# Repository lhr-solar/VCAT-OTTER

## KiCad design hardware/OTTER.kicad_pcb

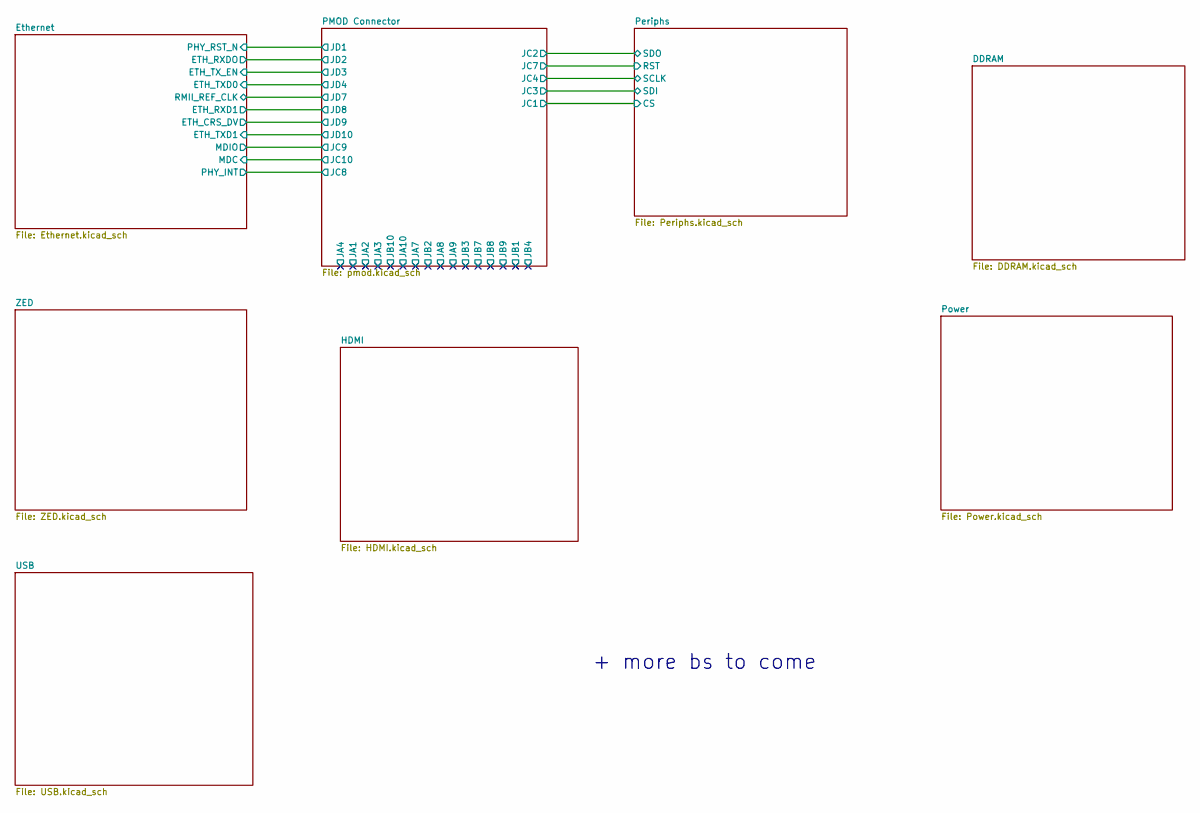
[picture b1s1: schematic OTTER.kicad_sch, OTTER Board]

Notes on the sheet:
+ more bs to come

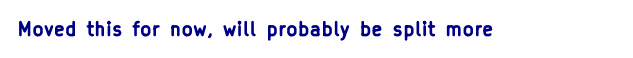
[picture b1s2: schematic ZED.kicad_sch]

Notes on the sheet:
Moved this for now, will probably be split more

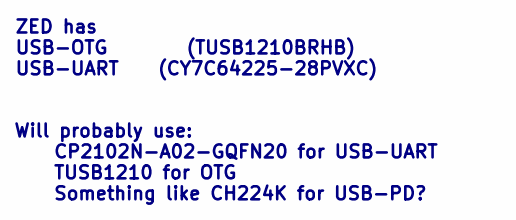
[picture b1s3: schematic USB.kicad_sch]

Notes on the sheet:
ZED has USB-OTG (TUSB1210BRHB) USB-UART (CY7C64225-28PVXC)
Will probably use: CP2102N-A02-GQFN20 for USB-UART TUSB1210 for OTG Something like CH224K for USB-PD?

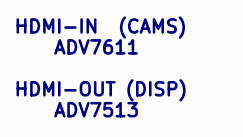
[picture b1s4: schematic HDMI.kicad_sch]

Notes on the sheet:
HDMI-IN (CAMS) ADV7611 HDMI-OUT (DISP) ADV7513

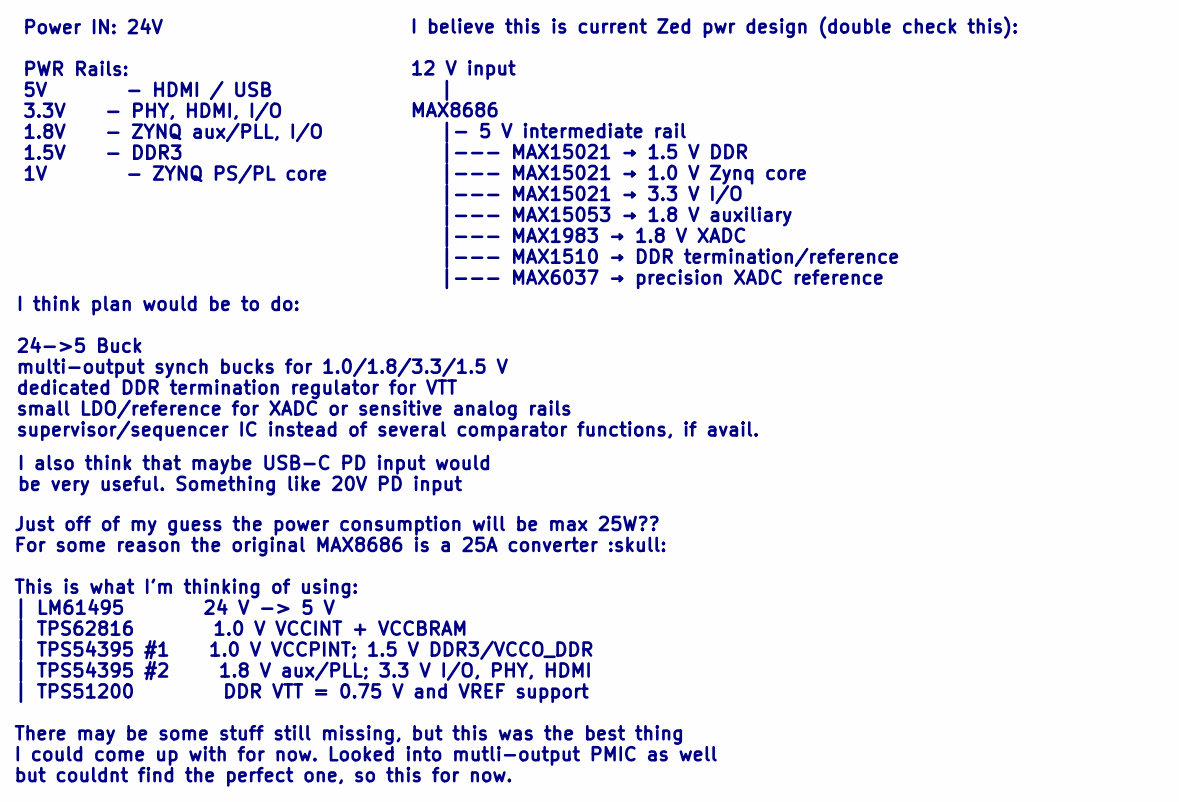
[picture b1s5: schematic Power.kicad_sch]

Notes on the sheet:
Just off of my guess the power consumption will be max 25W?? For some reason the original MAX8686 is a 25A converter :skull: This is what I'm thinking of using: | LM61495 24 V -> 5 V | TPS62816 1.0 V VCCINT + VCCBRAM | TPS54395 #1 1.0 V VCCPINT; 1.5 V DDR3/VCCO_DDR | TPS54395 #2 1.8 V aux/PLL; 3.3 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
Power IN: 24V PWR Rails: 5V - HDMI / USB 3.3V - PHY, HDMI, I/O 1.8V - ZYNQ aux/PLL, I/O 1.5V - DDR3 1V - ZYNQ PS/PL core
I think plan would be to do: 24->5 Buck multi-output synch bucks for 1.0/1.8/3.3/1.5 V dedicated DDR termination regulator for VTT small LDO/reference for XADC or sensitive analog rails supervisor/sequencer IC instead of several comparator functions, if avail.
I also think that maybe USB-C PD input would be very useful. Something like 20V PD input
I believe this is current Zed pwr design (double check this): 12 V input | MAX8686 |- 5 V intermediate rail |--- MAX15021 → 1.5 V DDR |--- MAX15021 → 1.0 V Zynq core |--- MAX15021 → 3.3 V I/O |--- MAX15053 → 1.8 V auxiliary |--- MAX1983 → 1.8 V XADC |--- MAX1510 → DDR termination/reference |--- MAX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

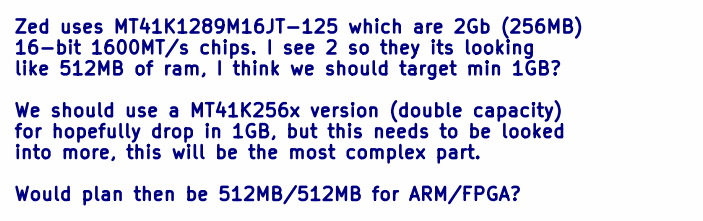
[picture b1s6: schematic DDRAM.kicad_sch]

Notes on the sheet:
Zed uses MT41K1289M16JT-125 which are 2Gb (256MB) 16-bit 1600MT/s chips. I see 2 so they its looking like 512MB of ram, I think we should target min 1GB? We should use a MT41K256x version (double capacity) for hopefully drop in 1GB, but this needs to be looked into more, this will be the most compl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

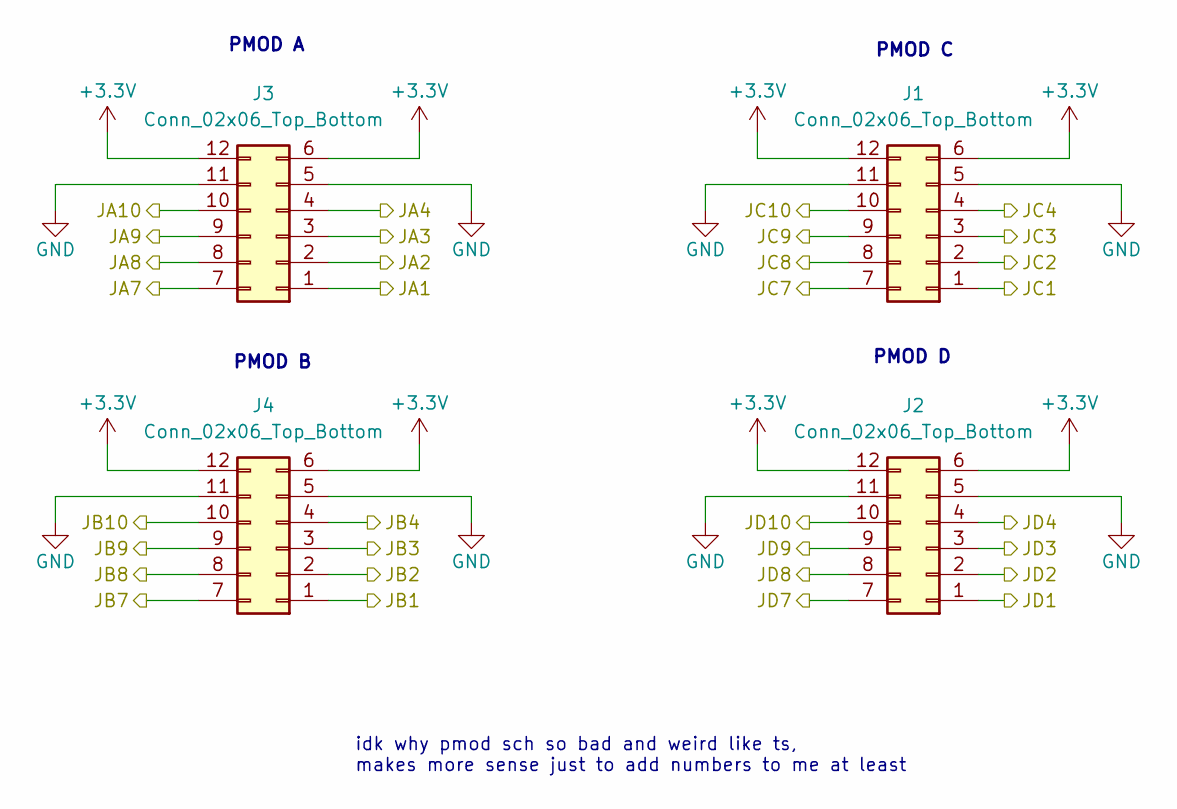
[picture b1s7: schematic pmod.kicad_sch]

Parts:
J1, J2, J3, J4: Conn_02x06_Top_Bottom; PinHeader_2x06_P2.54mm_Horizontal

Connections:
+3.3V: J1.6, J1.12, J2.6, J2.12, J3.6, J3.12, J4.6, J4.12; also elsewhere on the board
/Ethernet/ETH_CRS_DV: J2.9; also elsewhere on the board
/Ethernet/ETH_RXD1: J2.8; also elsewhere on the board
/Ethernet/ETH_RXDO: J2.2; also elsewhere on the board
/Ethernet/ETH_TXD0: J2.4; also elsewhere on the board
/Ethernet/ETH_TXD1: J2.10; also elsewhere on the board
/Ethernet/ETH_TX_EN: J2.3; also elsewhere on the board
/Ethernet/MDC: J1.10; also elsewhere on the board
/Ethernet/MDIO: J1.9; also elsewhere on the board
/Ethernet/PHY_INT: J1.8; also elsewhere on the board
/Ethernet/PHY_RST_N: J2.1; also elsewhere on the board
/Ethernet/RMII_REF_CLK: J2.7; also elsewhere on the board
/PMOD Connector/JC1: J1.1; also elsewhere on the board
/PMOD Connector/JC2: J1.2; also elsewhere on the board
/PMOD Connector/JC3: J1.3; also elsewhere on the board
/PMOD Connector/JC4: J1.4; also elsewhere on the board
/PMOD Connector/JC7: J1.7; also elsewhere on the board
GND: J1.5, J1.11, J2.5, J2.11, J3.5, J3.11, J4.5, J4.11; also elsewhere on the board

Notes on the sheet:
PMOD A
PMOD B
PMOD C
PMOD D
idk why pmod sch so bad and weird like ts, makes more sense just to add numbers to me at least

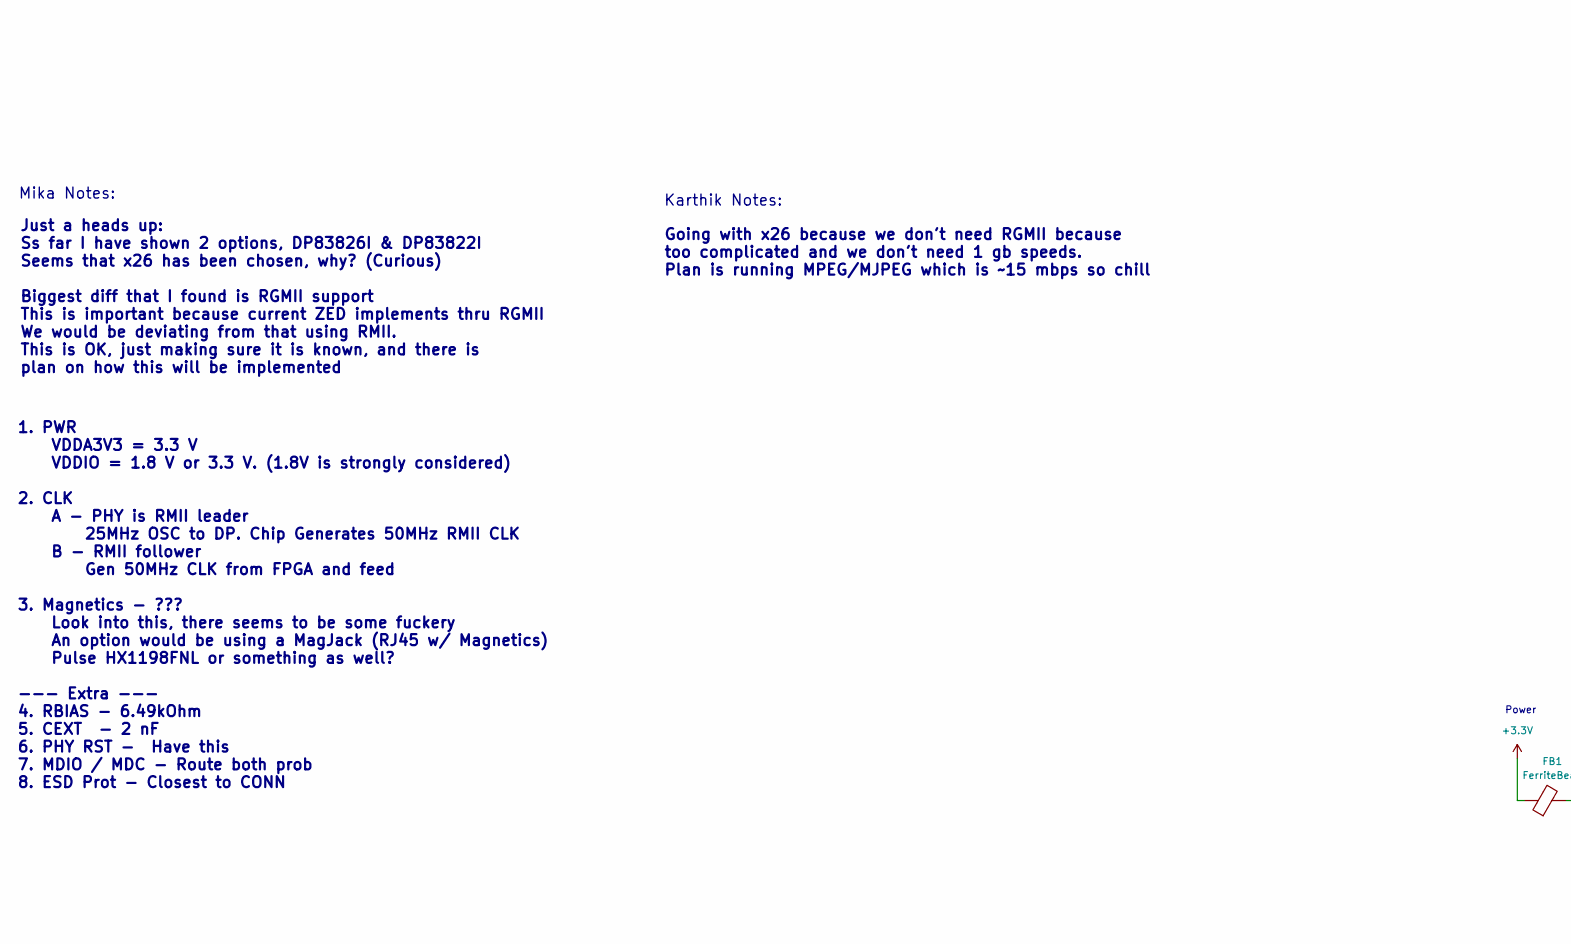
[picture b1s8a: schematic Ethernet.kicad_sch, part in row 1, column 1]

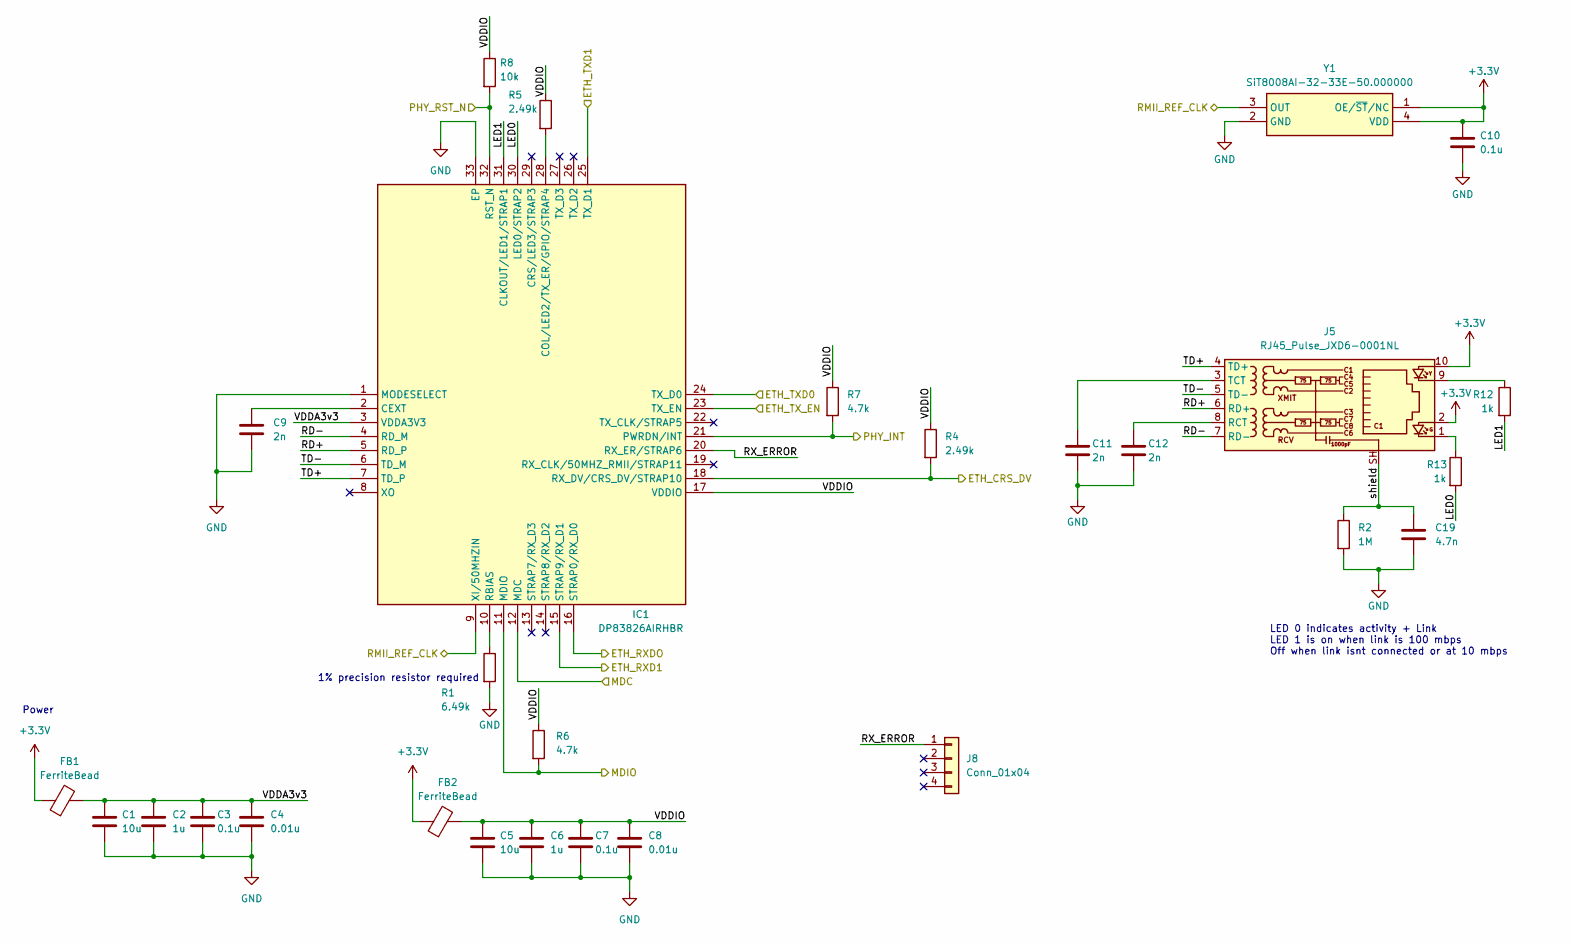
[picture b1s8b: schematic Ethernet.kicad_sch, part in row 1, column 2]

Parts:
C1, C5: 10u; C_0603_1608Metric_Pad1.08x0.95mm_HandSolder
C2, C6: 1u; C_0603_1608Metric_Pad1.08x0.95mm_HandSolder
C3, C7, C10: 0.1u; C_0603_1608Metric_Pad1.08x0.95mm_HandSolder
C4, C8: 0.01u; C_0603_1608Metric_Pad1.08x0.95mm_HandSolder
C9, C11, C12: 2n; C_0603_1608Metric_Pad1.08x0.95mm_HandSolder
C19: 4.7n; C_0603_1608Metric_Pad1.08x0.95mm_HandSolder
FB1, FB2: FerriteBead; C_0603_1608Metric_Pad1.08x0.95mm_HandSolder
IC1: DP83826AIRHBR; QFN50P500X500X100-33N-D; Manufacturer_Part_Number DP83826AIRHBR
J5: RJ45_Pulse_JXD6-0001NL; RJ45_Pulse_JXD6-0001NL_Horizontal
J8: Conn_01x04; PinHeader_1x04_P2.54mm_Vertical
R1: 6.49k; R_0603_1608Metric_Pad0.98x0.95mm_HandSolder
R2: 1M; R_0603_1608Metric_Pad0.98x0.95mm_HandSolder
R4, R5: 2.49k; R_0603_1608Metric_Pad0.98x0.95mm_HandSolder
R6, R7: 4.7k; R_0603_1608Metric_Pad0.98x0.95mm_HandSolder
R8: 10k; R_0603_1608Metric_Pad0.98x0.95mm_HandSolder
R12, R13: 1k; R_0603_1608Metric_Pad0.98x0.95mm_HandSolder
Y1: SiT8008AI-32-33E-50.000000; SiT8921BM3233N127872000; Manufacturer_Part_Number SiT8008AI-32-33E-50.000000

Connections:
+3.3V: C10.1, FB1.1, FB2.1, J5.2, J5.10, Y1.1 (OE/~ST/NC), Y1.4 (VDD); also elsewhere on the board
/Ethernet/ETH_CRS_DV: IC1.18 (RX_DV/CRS_DV/STRAP10), R4.2; also elsewhere on the board
/Ethernet/ETH_RXD1: IC1.15 (STRAP9/RX_D1); also elsewhere on the board
/Ethernet/ETH_RXDO: IC1.16 (STRAP0/RX_D0); also elsewhere on the board
/Ethernet/ETH_TXD0: IC1.24 (TX_D0); also elsewhere on the board
/Ethernet/ETH_TXD1: IC1.25 (TX_D1); also elsewhere on the board
/Ethernet/ETH_TX_EN: IC1.23 (TX_EN); also elsewhere on the board
/Ethernet/LED0: IC1.30 (LED0/STRAP2), R13.2
/Ethernet/LED1: IC1.31 (CLKOUT/LED1/STRAP1), R12.2
/Ethernet/MDC: IC1.12 (MDC); also elsewhere on the board
/Ethernet/MDIO: IC1.11 (MDIO), R6.2; also elsewhere on the board
/Ethernet/PHY_INT: IC1.21 (PWRDN/INT), R7.2; also elsewhere on the board
/Ethernet/PHY_RST_N: IC1.32 (RST_N), R8.2; also elsewhere on the board
/Ethernet/RD+: IC1.5 (RD_P), J5.6 (RD+)
/Ethernet/RD-: IC1.4 (RD_M), J5.7 (RD-)
/Ethernet/RMII_REF_CLK: IC1.9 (XI/50MHZIN), Y1.3 (OUT); also elsewhere on the board
/Ethernet/RX_ERROR: IC1.20 (RX_ER/STRAP6), J8.1
/Ethernet/TD+: IC1.7 (TD_P), J5.4 (TD+)
/Ethernet/TD-: IC1.6 (TD_M), J5.5 (TD-)
/Ethernet/VDDA3v3: C1.1, C2.1, C3.1, C4.1, FB1.2, IC1.3 (VDDA3V3)
/Ethernet/VDDIO: C5.1, C6.1, C7.1, C8.1, FB2.2, IC1.17 (VDDIO), R4.1, R5.1, R6.1, R7.1, R8.1
/Ethernet/shield: C19.1, J5.SH, R2.1
GND: C1.2, C2.2, C3.2, C4.2, C5.2, C6.2, C7.2, C8.2, C9.2, C10.2, C11.2, C12.2, C19.2, IC1.1 (MODESELECT), IC1.33 (EP), R1.2, R2.2, Y1.2 (GND); also elsewhere on the board
unnamed: C9.1, IC1.2 (CEXT)
unnamed: IC1.28 (COL/LED2/TX_ER/GPIO/STRAP4), R5.2
unnamed: IC1.10 (RBIAS), R1.1
unnamed: J5.1, R13.1
unnamed: J5.9, R12.1
unnamed: C12.1, J5.8 (RCT)
unnamed: C11.1, J5.3 (TCT)

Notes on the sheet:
Going with x26 because we don't need RGMII because too complicated and we don't need 1 gb speeds. Plan is running MPEG/MJPEG which is ~15 mbps so chill
1% precision resistor required
1. PWR VDDA3V3 = 3.3 V VDDIO = 1.8 V or 3.3 V. (1.8V is strongly considered) 2. CLK A - PHY is RMII leader 25MHz OSC to DP. Chip Generates 50MHz RMII CLK B - RMII follower Gen 50MHz CLK from FPGA and feed 3. Magnetics - ??? Look into this, there seems to be some fuckery An option would be using a M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
Mika Notes:
Karthik Notes:
Power
Just a heads up: Ss far I have shown 2 options, DP83826I & DP83822I Seems that x26 has been chosen, why? (Curious) Biggest diff that I found is RGMII support This is important because current ZED implements thru RGMII We would be deviating from that using RMII. This is OK, just making sure it is kn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
LED 0 indicates activity + Link LED 1 is on when link is 100 mbps Off when link isnt connected or at 10 mbps

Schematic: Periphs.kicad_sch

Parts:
C13, C15, C17: 10u; C_0603_1608Metric_Pad1.08x0.95mm_HandSolder
C14, C16: 100n; C_0603_1608Metric_Pad1.08x0.95mm_HandSolder
C18: 330n; C_0603_1608Metric_Pad1.08x0.95mm_HandSolder
C20, C21: 10p; C_0603_1608Metric_Pad1.08x0.95mm_HandSolder
J6: Conn_01x04; PinSocket_1x04_P2.54mm_Vertical
JP1: Jumper_2_Small_Open; PinHeader_1x02_P2.54mm_Vertical
R3: 120; R_0603_1608Metric_Pad0.98x0.95mm_HandSolder
R9, R10: 10k; R_0603_1608Metric_Pad0.98x0.95mm_HandSolder
R18, R19, R20, R21: 22; R_0603_1608Metric_Pad0.98x0.95mm_HandSolder
U1: TCAN4551RGYRQ1; Texas_RGY_R-PVQFN-N20_EP2.05x3.05mm
U2: USBLC6-4SC6; SOT-23-6
Y3: 7M40000005; 7M27120MAAJT

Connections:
+3.3V: C13.1, C14.1, R9.1, U1.17 (V_{IO}), U2.5 (VBUS); also elsewhere on the board
+20V: C15.1, C16.1, J6.4, U1.14 (V_{SUP}); also elsewhere on the board
/PMOD Connector/JC1: R9.2, R21.1, U2.6 (I/O4); also elsewhere on the board
/PMOD Connector/JC2: R20.1, U2.4 (I/O3); also elsewhere on the board
/PMOD Connector/JC3: R19.1, U2.3 (I/O2); also elsewhere on the board
/PMOD Connector/JC4: R18.1, U2.1 (I/O1); also elsewhere on the board
/PMOD Connector/JC7: R10.1, U1.19 (RST); also elsewhere on the board
/Periphs/CAN_H: J6.2, JP1.1 (A), U1.11 (CANH)
/Periphs/CAN_L: J6.1, R3.2, U1.10 (CANL)
GND: C13.2, C14.2, C15.2, C16.2, C17.2, C18.2, C20.2, C21.2, J6.3, R10.2, U1.12 (WAKE), U1.13 (GND), U1.21 (GND), U2.2 (GND), Y3.2 (G), Y3.4 (G); also elsewhere on the board
unnamed: JP1.2 (B), R3.1
unnamed: C18.1, U1.18 (FLTR)
unnamed: C20.1, U1.1 (OSC1), Y3.1
unnamed: C21.1, U1.20 (OSC2), Y3.3
unnamed: R18.2, U1.4 (SCLK)
unnamed: R19.2, U1.5 (SDI)
unnamed: R20.2, U1.6 (SDO)
unnamed: C17.1, U1.16 (V_{CCFLTR})
unnamed: R21.2, U1.7 (~CS)

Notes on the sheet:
add power protection block
ESD Protection
CAN -> SPI TCAN4550-Q1 Add ESD/TVS for accidental 24V on CAN line
clock needs to be 40mhz i cant find anything

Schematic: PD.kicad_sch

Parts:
C22: 1u; C_0603_1608Metric_Pad1.08x0.95mm_HandSolder
D1: LED; LED_0603_1608Metric_Pad1.05x0.95mm_HandSolder
F1: Fuse; C_0603_1608Metric_Pad1.08x0.95mm_HandSolder
J7: USB_C_Receptacle_USB2.0_14P; USB_C_Receptacle_GCT_USB4105-xx-A_16P_TopMnt_Horizontal
R11: R; R_0603_1608Metric_Pad0.98x0.95mm_HandSolder
R14, R15: 5.1k; R_0603_1608Metric_Pad0.98x0.95mm_HandSolder
R16: 1k; R_0603_1608Metric_Pad0.98x0.95mm_HandSolder
R17: 200k; R_0603_1608Metric_Pad0.98x0.95mm_HandSolder
U4: CH221K; SOT-23-6

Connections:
+3.3V: R11.1; also elsewhere on the board
+20V: F1.2; also elsewhere on the board
/Periphs/USBPD/PG: D1.1 (K), U4.3 (~PG)
/Periphs/USBPD/VDD: C22.1, R16.1, R17.1, U4.1 (VDD)
GND: C22.2, J7.A1 (GND), J7.A12 (GND), J7.B1 (GND), J7.B12 (GND), R14.2, R15.2, U4.2 (GND); also elsewhere on the board
unnamed: D1.2 (A), R11.2
unnamed: J7.A5 (CC1), R14.1, U4.4 (CC1)
unnamed: J7.B5 (CC2), R15.1, U4.5 (CC2)
unnamed: R17.2, U4.6 (CFG)
VBUS: F1.1, J7.A4 (VBUS), J7.A9 (VBUS), J7.B4 (VBUS), J7.B9 (VBUS), R16.2

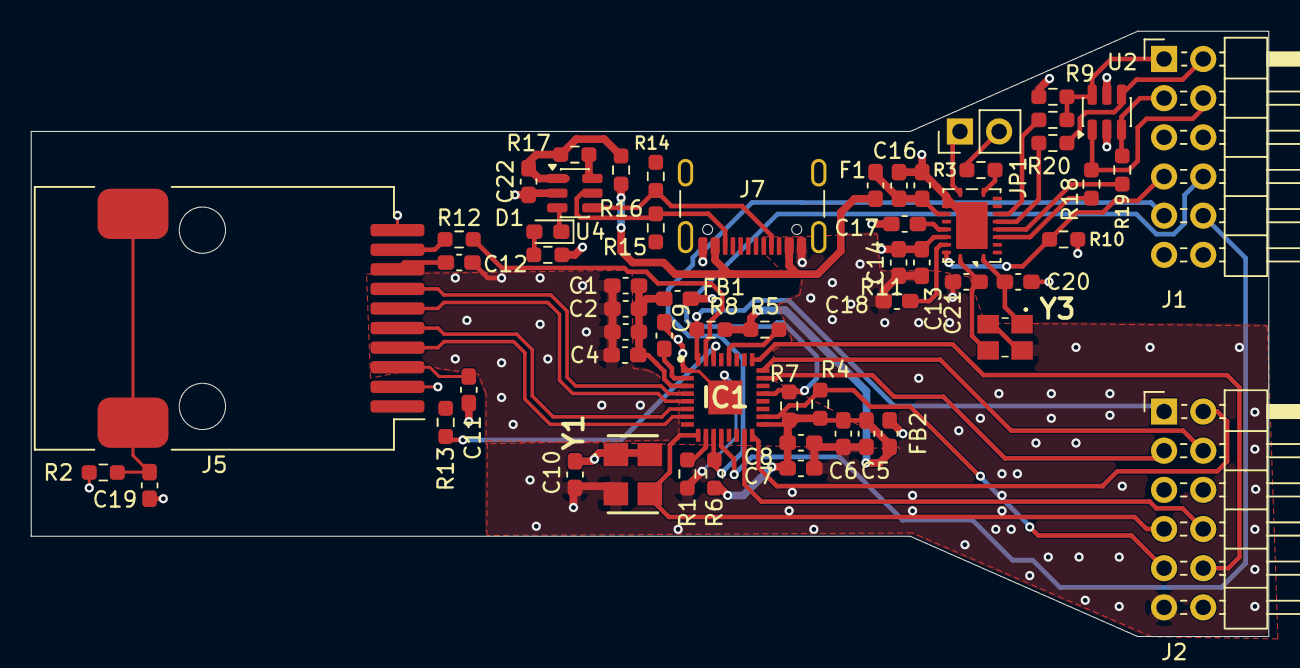
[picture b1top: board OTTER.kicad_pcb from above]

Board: 4 copper layers, 80.2 x 39.2 mm, 58 parts (0 on the bottom side), 53 nets.
